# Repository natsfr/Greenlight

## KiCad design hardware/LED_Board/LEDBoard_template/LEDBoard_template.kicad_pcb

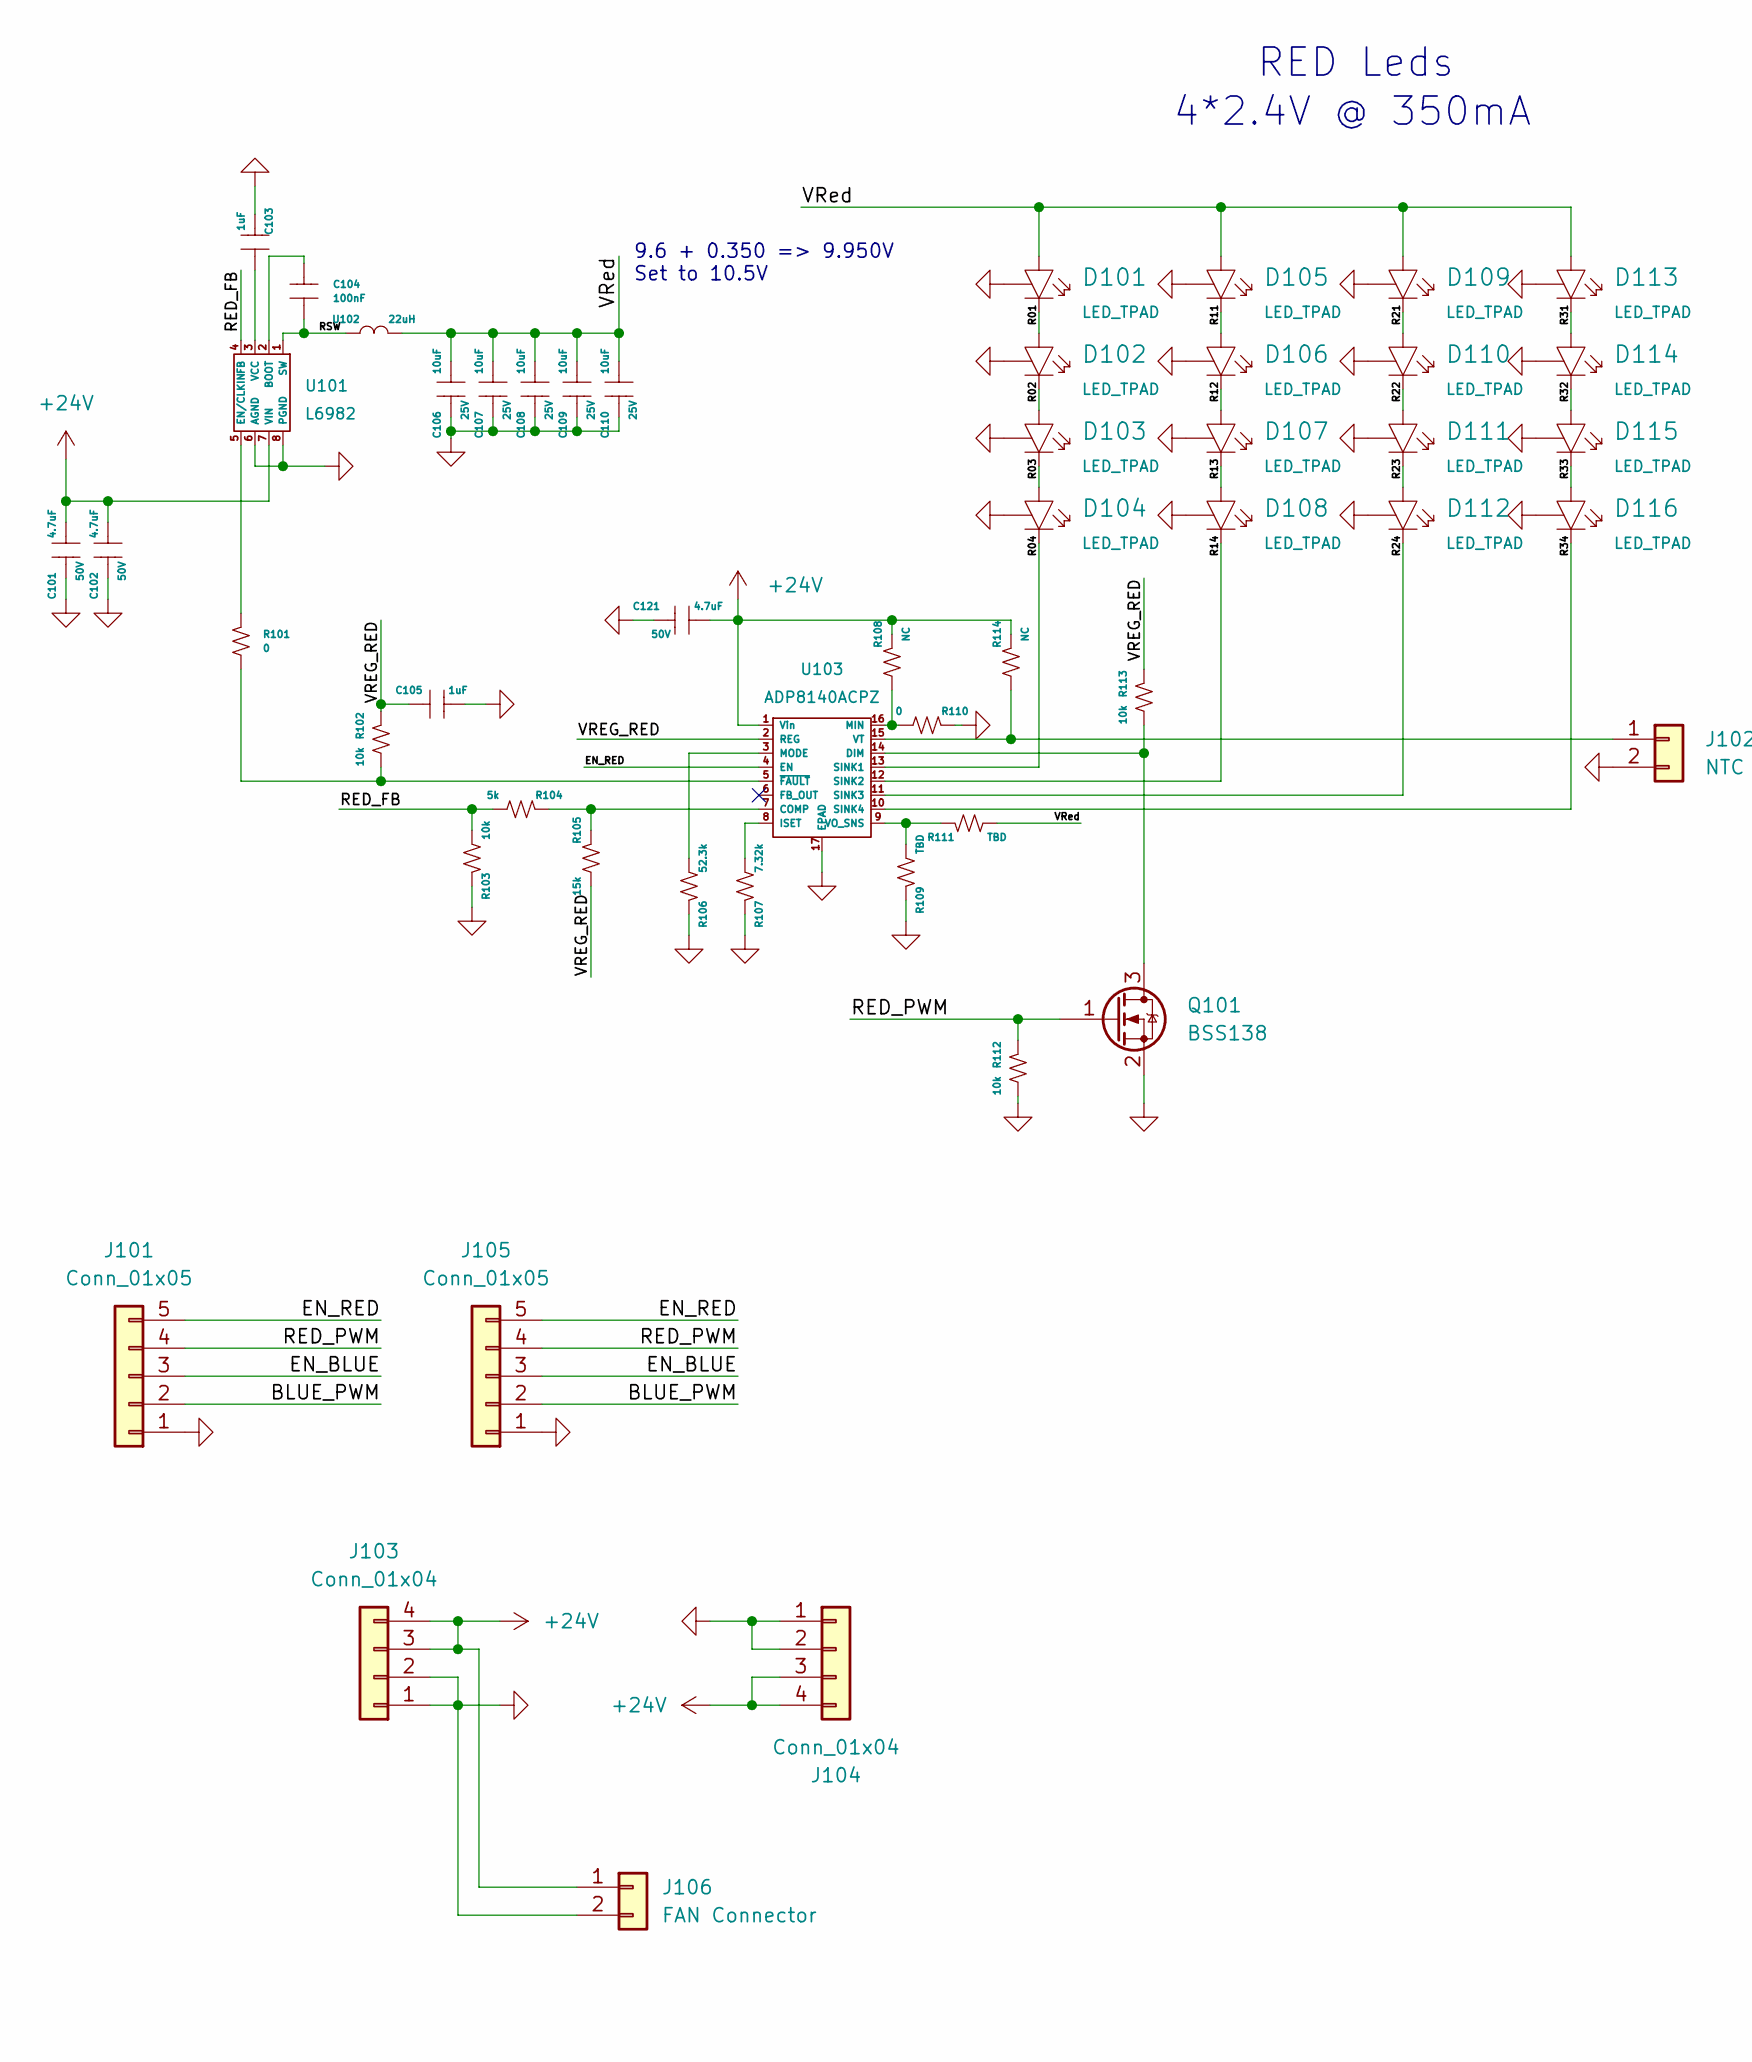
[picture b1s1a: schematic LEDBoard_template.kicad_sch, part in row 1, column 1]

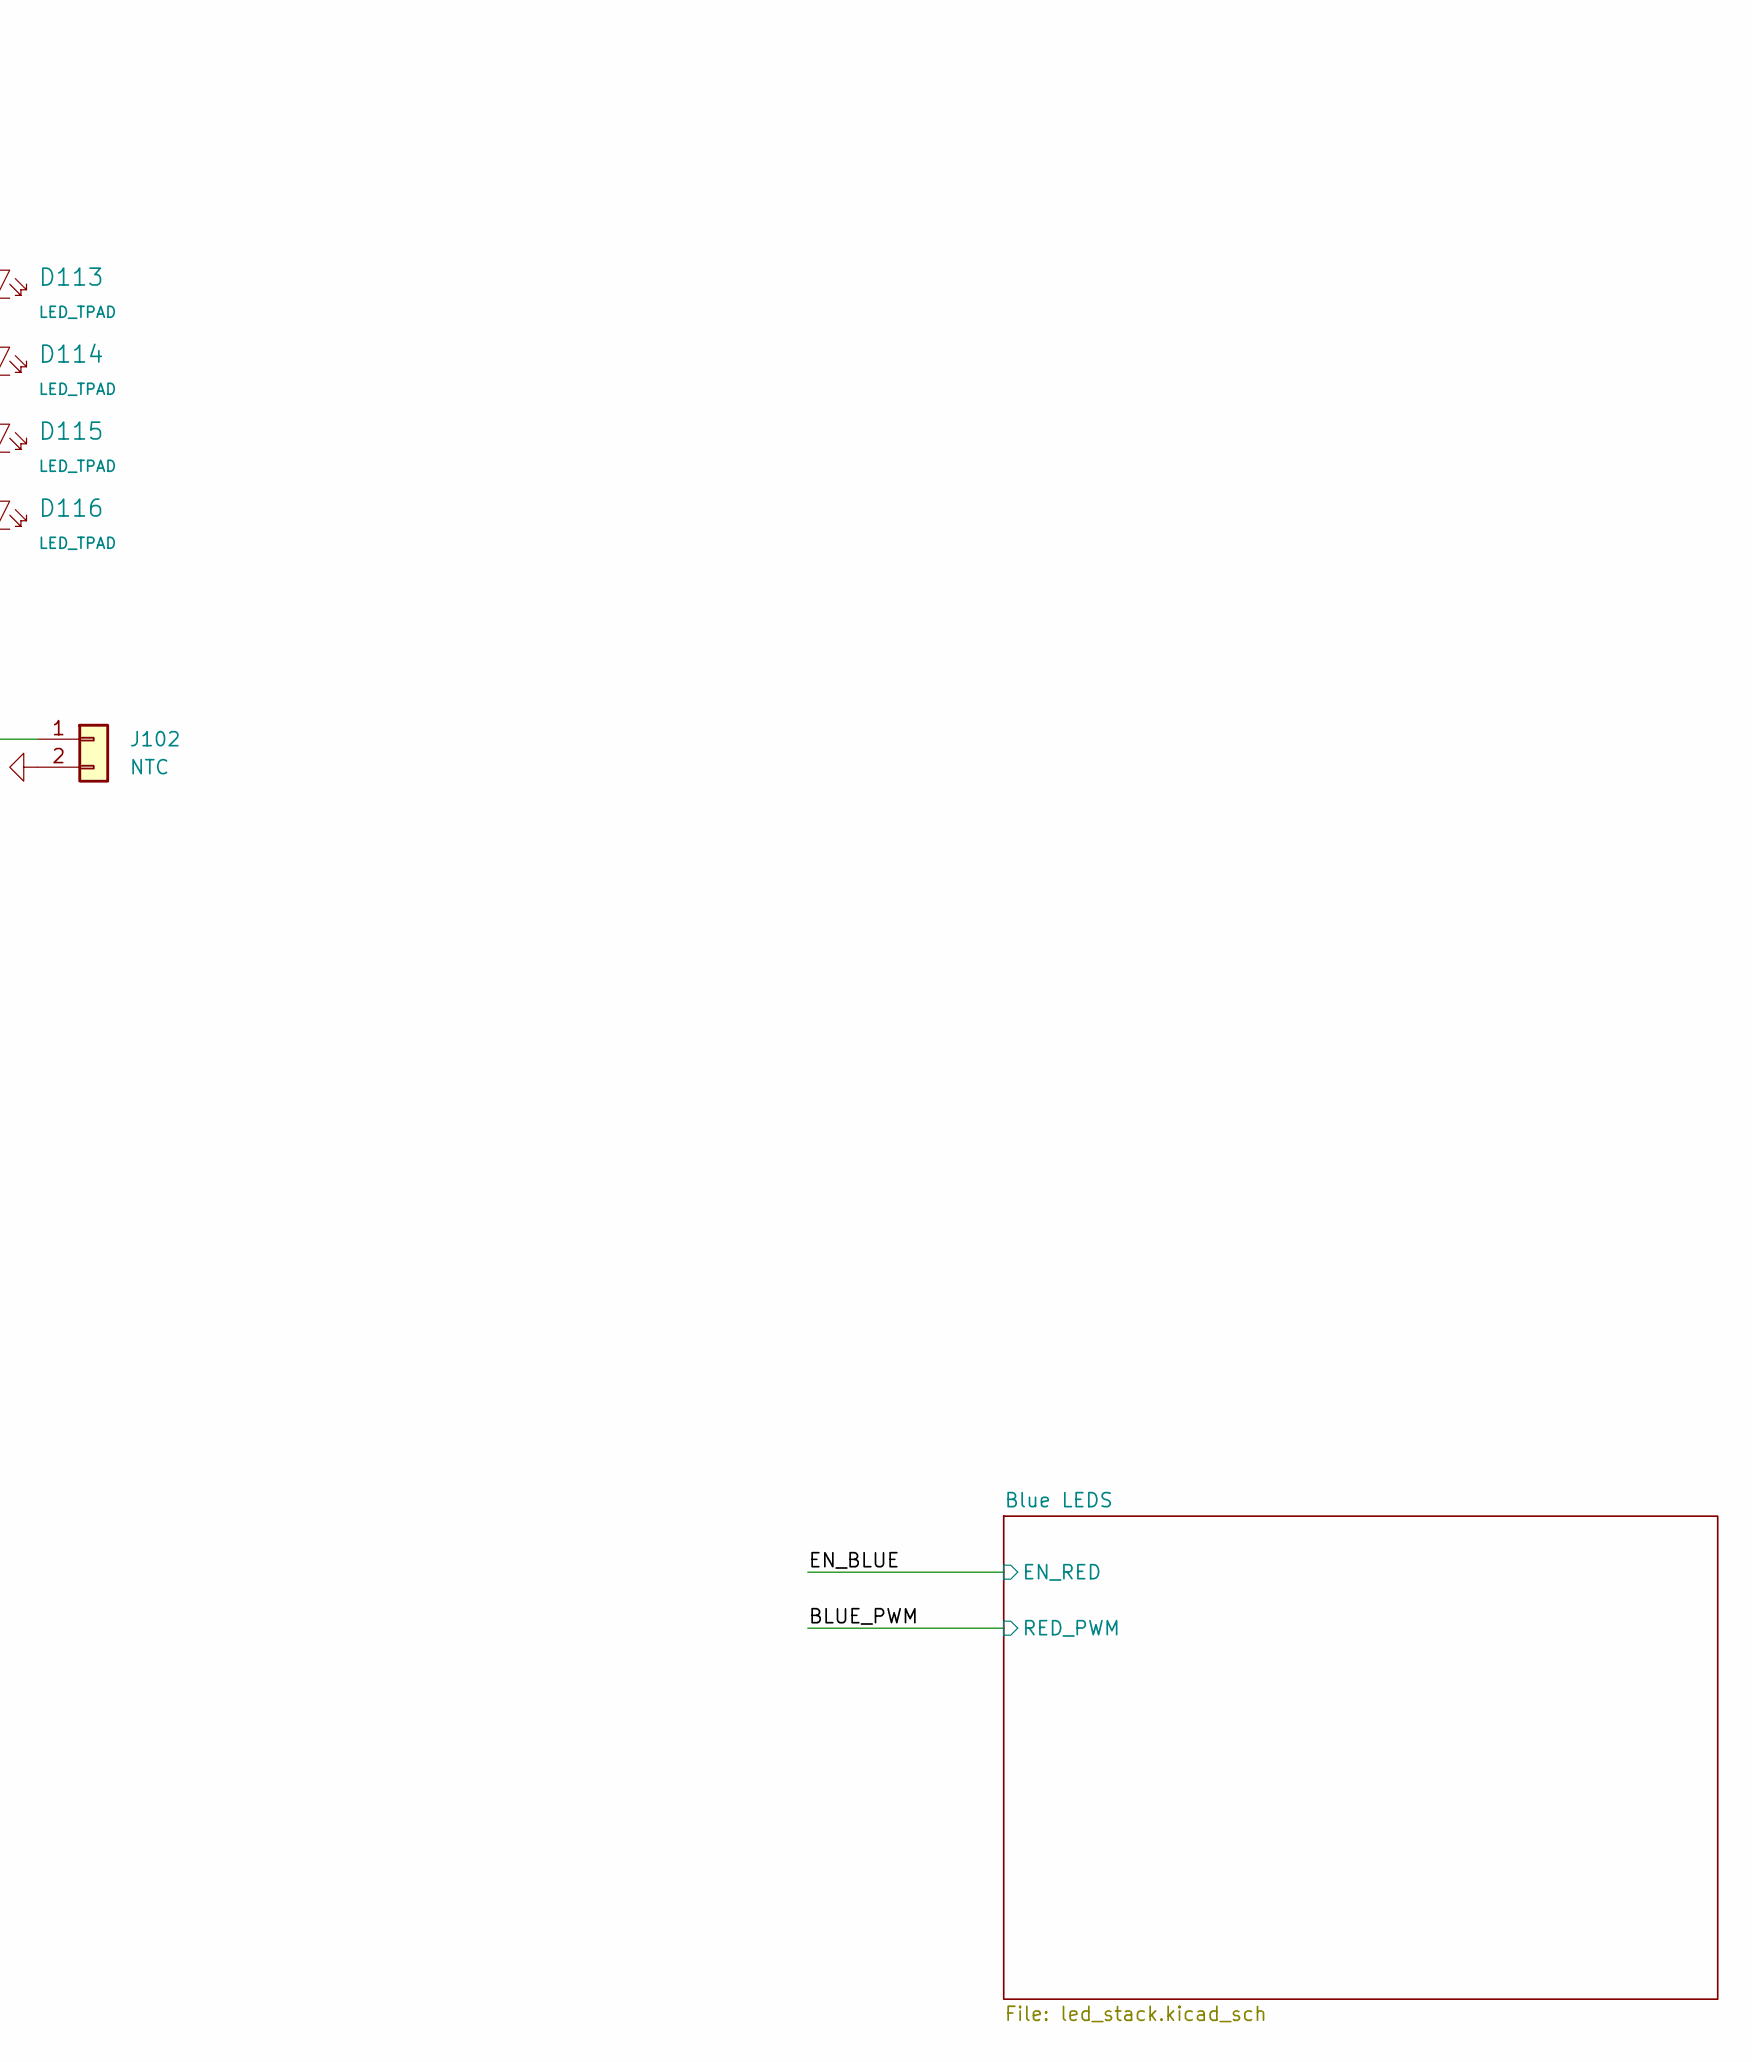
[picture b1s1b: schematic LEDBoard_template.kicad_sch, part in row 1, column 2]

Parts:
C101, C102, C121: 4.7uF; SM1206
C103, C105: 1uF; SM0805
C104: 100nF; SM0603
C106, C107, C108, C109, C110: 10uF; SM1206
D101, D102, D103, D104, D105, D106, D107, D108, D109, D110, D111, D112, D113, D114, D115, D116: LED_TPAD; XLamp_MLE
J101, J105: Conn_01x05; JST_XH_B5B-XH-A_1x05_P2.50mm_Vertical
J102: NTC; JST_XH_B2B-XH-A_1x02_P2.50mm_Vertical
J103, J104: Conn_01x04; MICROFIT_4POS_FEM_43650-0403
J106: FAN Connector; JST_XH_B2B-XH-A_1x02_P2.50mm_Vertical
Q101: BSS138; SOT-23
R101, R110: 0; SM0603
R102, R103, R112, R113: 10k; SM0603
R104: 5k; SM0603
R105: 15k; SM0603
R106: 52.3k; SM0603
R107: 7.32k; SM0603
R108, R114: NC; SM0603
R109, R111: TBD; SM0603
U101: L6982; SOIC-8_208mil
U102: 22uH; IND_SRP8540A_8.1x8.4x3.8mm
U103: ADP8140ACPZ; ADP8140_LFCSP16_4x4_0.4mm

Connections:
+24V: C101.1, C102.1, C121.1, J103.3, J103.4, J104.3, J104.4, J106.1, R108.2, R114.2, U101.7 (VIN), U103.1 (Vin); also elsewhere on the board
/BLUE_PWM: J101.2, J105.2; also elsewhere on the board
/EN_BLUE: J101.3, J105.3; also elsewhere on the board
/EN_RED: J101.5, J105.5, U103.4 (EN)
/R01: D101.K, D102.A
/R02: D102.K, D103.A
/R03: D103.K, D104.A
/R04: D104.K, U103.13 (SINK1)
/R11: D105.K, D106.A
/R12: D106.K, D107.A
/R13: D107.K, D108.A
/R14: D108.K, U103.12 (SINK2)
/R21: D109.K, D110.A
/R22: D110.K, D111.A
/R23: D111.K, D112.A
/R24: D112.K, U103.11 (SINK3)
/R31: D113.K, D114.A
/R32: D114.K, D115.A
/R33: D115.K, D116.A
/R34: D116.K, U103.10 (SINK4)
/RED_FB: R103.1, R104.1, U101.4 (FB)
/RED_PWM: J101.4, J105.4, Q101.1 (G), R112.2
/RSW: C104.1, U101.1 (SW), U102.1
/VREG_RED: C105.1, R102.2, R105.1, R113.2, U103.2 (REG)
/VRed: C106.1, C107.1, C108.1, C109.1, C110.1, D101.A, D105.A, D109.A, D113.A, R111.1, U102.2
GND: C101.2, C102.2, C103.2, C105.2, C106.2, C107.2, C108.2, C109.2, C110.2, C121.2, D101.N (PAD), D102.N (PAD), D103.N (PAD), D104.N (PAD), D105.N (PAD), D106.N (PAD), D107.N (PAD), D108.N (PAD), D109.N (PAD), D110.N (PAD), D111.N (PAD), D112.N (PAD), D113.N (PAD), D114.N (PAD), D115.N (PAD), D116.N (PAD), J101.1, J102.2, J103.1, J103.2, J104.1, J104.2, J105.1, J106.2, Q101.2 (S), R103.2, R106.2, R107.2, R109.2, R110.2, R112.1, U101.6 (AGND), U101.8 (PGND), U103.17 (EPAD); also elsewhere on the board
unnamed: C103.1, U101.3 (VCC)
unnamed: C104.2, U101.2 (BOOT)
unnamed: J102.1, R114.1, U103.15 (VT)
unnamed: Q101.3 (D), R113.1, U103.14 (DIM)
unnamed: R101.1, R102.1, U103.5 (~FAULT)
unnamed: R101.2, U101.5 (EN/CLKIN)
unnamed: R104.2, R105.2, U103.7 (COMP)
unnamed: R106.1, U103.3 (MODE)
unnamed: R107.1, U103.8 (ISET)
unnamed: R108.1, R110.1, U103.16 (MIN)
unnamed: R109.1, R111.2, U103.9 (VO_SNS)

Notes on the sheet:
9.6 + 0.350 => 9.950V Set to 10.5V
4*2.4V @ 350mA
RED Leds

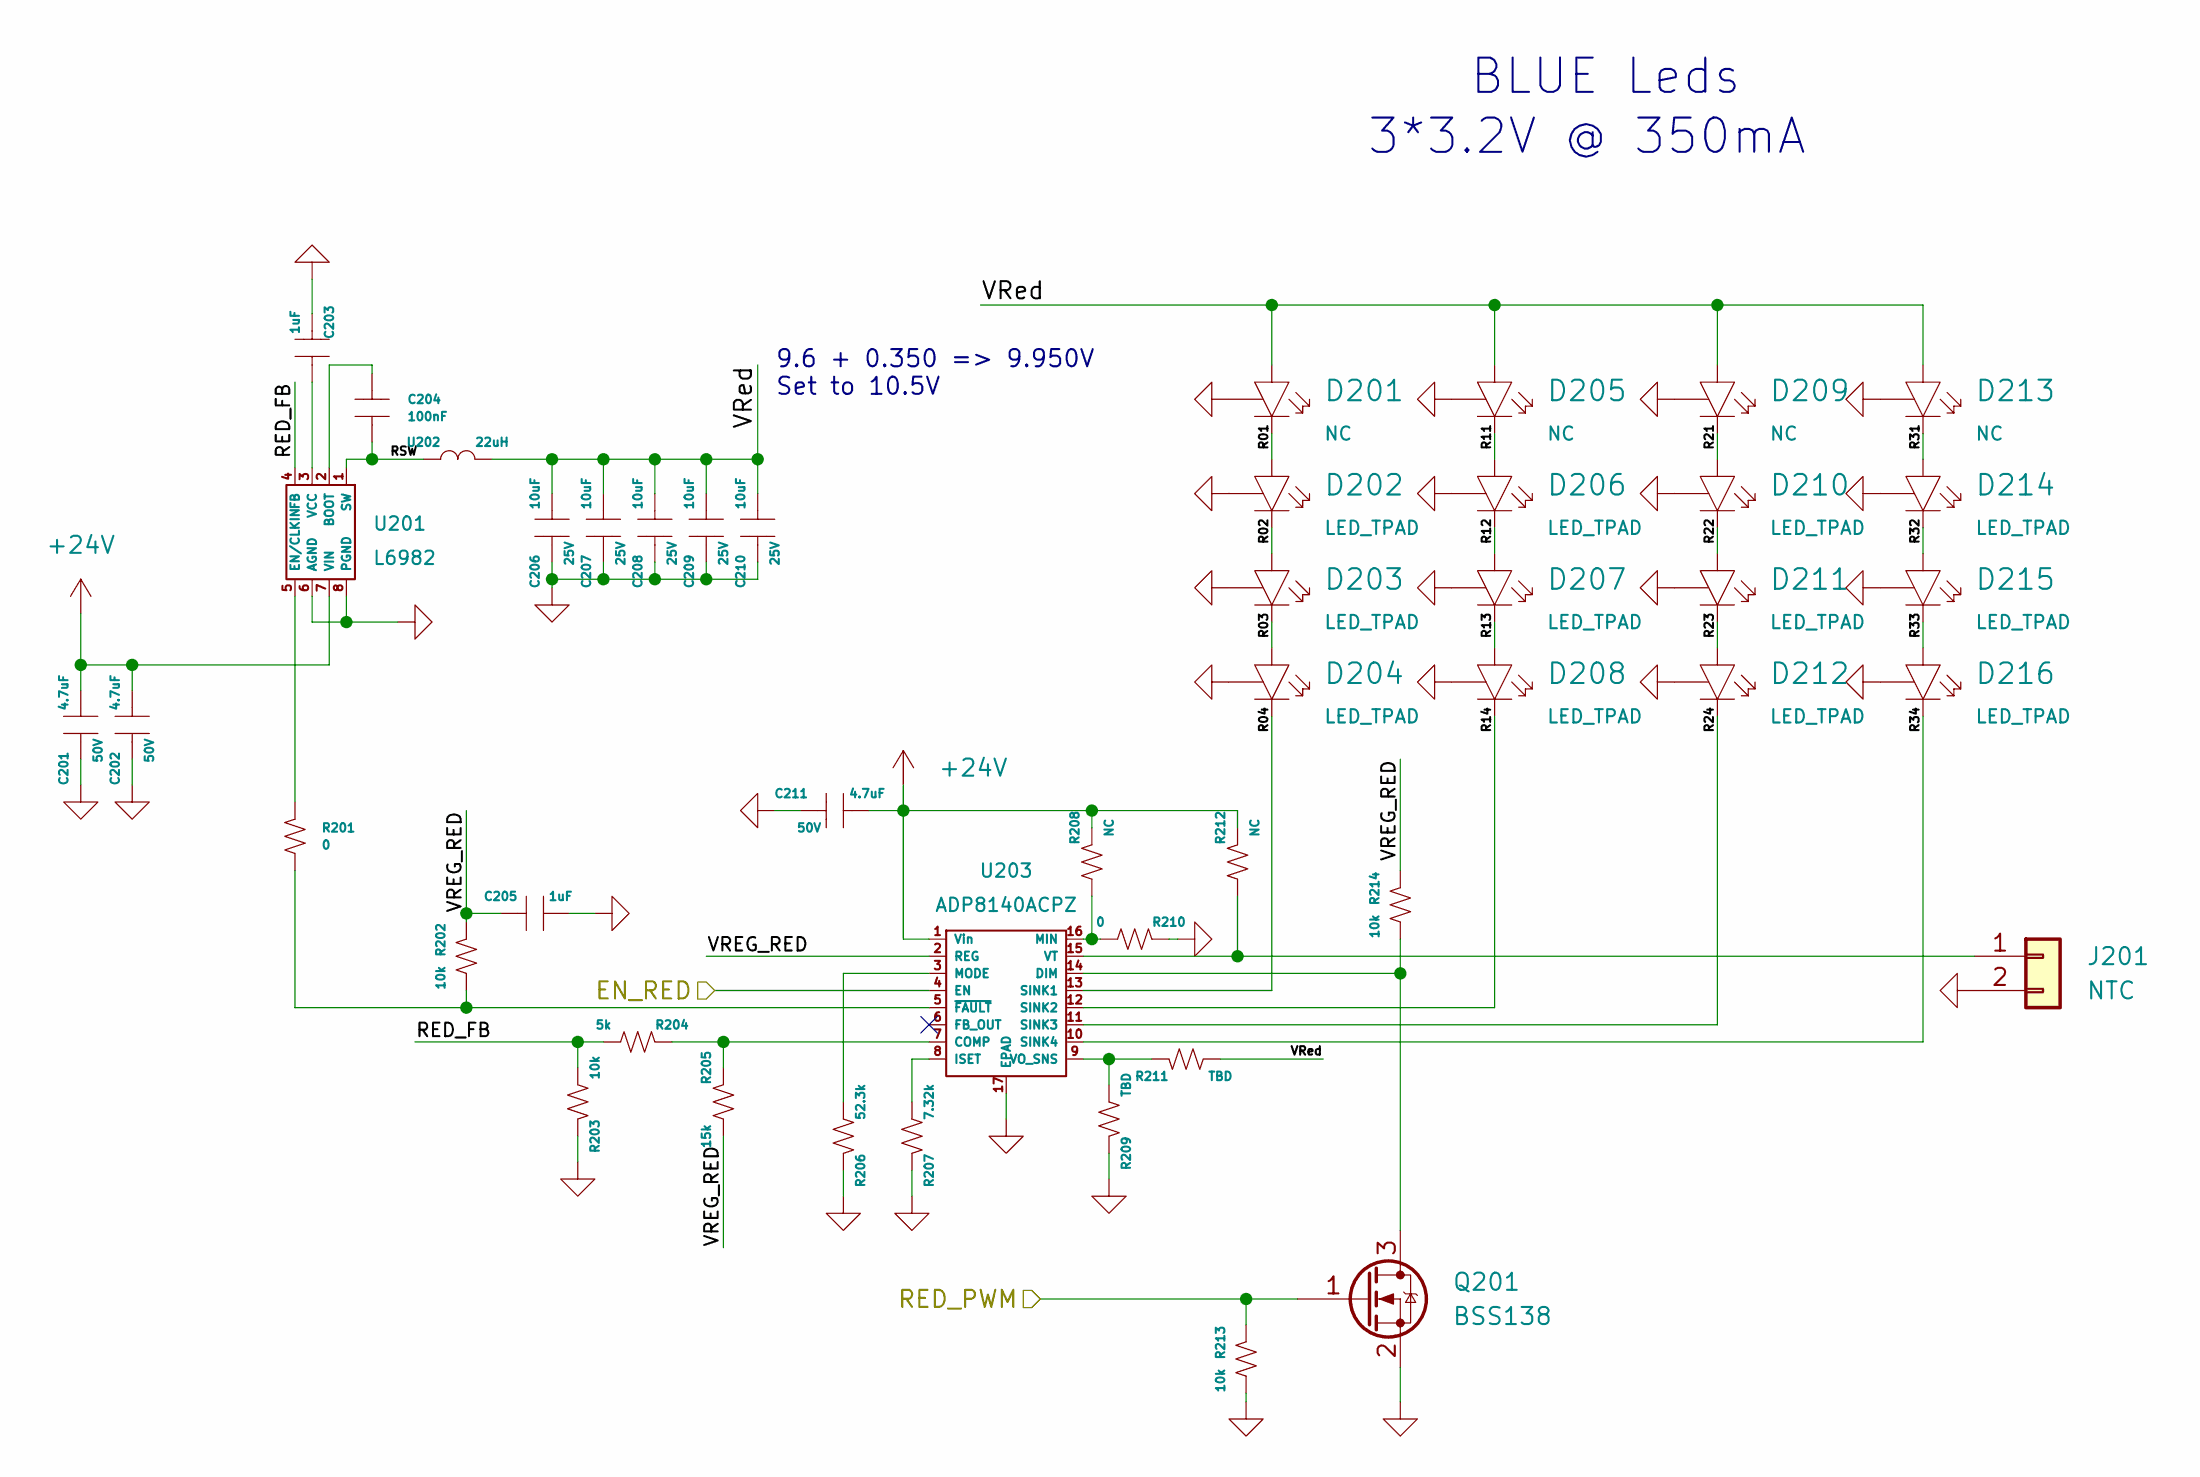
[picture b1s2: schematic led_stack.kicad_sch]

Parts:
C201, C202, C211: 4.7uF; SM1206
C203, C205: 1uF; SM0805
C204: 100nF; SM0603
C206, C207, C208, C209, C210: 10uF; SM1206
D201, D205, D209, D213: NC; XLamp_MLE
D202, D203, D204, D206, D207, D208, D210, D211, D212, D214, D215, D216: LED_TPAD; XLamp_MLE
J201: NTC; JST_XH_B2B-XH-A_1x02_P2.50mm_Vertical
Q201: BSS138; SOT-23
R201, R210: 0; SM0603
R202, R203, R213, R214: 10k; SM0603
R204: 5k; SM0603
R205: 15k; SM0603
R206: 52.3k; SM0603
R207: 7.32k; SM0603
R208, R212: NC; SM0603
R209, R211: TBD; SM0603
U201: L6982; SOIC-8_208mil
U202: 22uH; IND_SRP8540A_8.1x8.4x3.8mm
U203: ADP8140ACPZ; ADP8140_LFCSP16_4x4_0.4mm

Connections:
+24V: C201.1, C202.1, C211.1, R208.2, R212.2, U201.7 (VIN), U203.1 (Vin); also elsewhere on the board
/BLUE_PWM: Q201.1 (G), R213.2; also elsewhere on the board
/Blue LEDS/R01: D201.K, D202.A
/Blue LEDS/R02: D202.K, D203.A
/Blue LEDS/R03: D203.K, D204.A
/Blue LEDS/R04: D204.K, U203.13 (SINK1)
/Blue LEDS/R11: D205.K, D206.A
/Blue LEDS/R12: D206.K, D207.A
/Blue LEDS/R13: D207.K, D208.A
/Blue LEDS/R14: D208.K, U203.12 (SINK2)
/Blue LEDS/R21: D209.K, D210.A
/Blue LEDS/R22: D210.K, D211.A
/Blue LEDS/R23: D211.K, D212.A
/Blue LEDS/R24: D212.K, U203.11 (SINK3)
/Blue LEDS/R31: D213.K, D214.A
/Blue LEDS/R32: D214.K, D215.A
/Blue LEDS/R33: D215.K, D216.A
/Blue LEDS/R34: D216.K, U203.10 (SINK4)
/Blue LEDS/RED_FB: R203.1, R204.1, U201.4 (FB)
/Blue LEDS/RSW: C204.1, U201.1 (SW), U202.1
/Blue LEDS/VREG_RED: C205.1, R202.2, R205.1, R214.2, U203.2 (REG)
/Blue LEDS/VRed: C206.1, C207.1, C208.1, C209.1, C210.1, D201.A, D205.A, D209.A, D213.A, R211.1, U202.2
/EN_BLUE: U203.4 (EN); also elsewhere on the board
GND: C201.2, C202.2, C203.2, C205.2, C206.2, C207.2, C208.2, C209.2, C210.2, C211.2, D201.N (PAD), D202.N (PAD), D203.N (PAD), D204.N (PAD), D205.N (PAD), D206.N (PAD), D207.N (PAD), D208.N (PAD), D209.N (PAD), D210.N (PAD), D211.N (PAD), D212.N (PAD), D213.N (PAD), D214.N (PAD), D215.N (PAD), D216.N (PAD), J201.2, Q201.2 (S), R203.2, R206.2, R207.2, R209.2, R210.2, R213.1, U201.6 (AGND), U201.8 (PGND), U203.17 (EPAD); also elsewhere on the board
unnamed: C203.1, U201.3 (VCC)
unnamed: C204.2, U201.2 (BOOT)
unnamed: J201.1, R212.1, U203.15 (VT)
unnamed: Q201.3 (D), R214.1, U203.14 (DIM)
unnamed: R201.1, R202.1, U203.5 (~FAULT)
unnamed: R201.2, U201.5 (EN/CLKIN)
unnamed: R204.2, R205.2, U203.7 (COMP)
unnamed: R206.1, U203.3 (MODE)
unnamed: R207.1, U203.8 (ISET)
unnamed: R208.1, R210.1, U203.16 (MIN)
unnamed: R209.1, R211.2, U203.9 (VO_SNS)

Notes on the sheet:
BLUE Leds
3*3.2V @ 350mA
9.6 + 0.350 => 9.950V Set to 10.5V

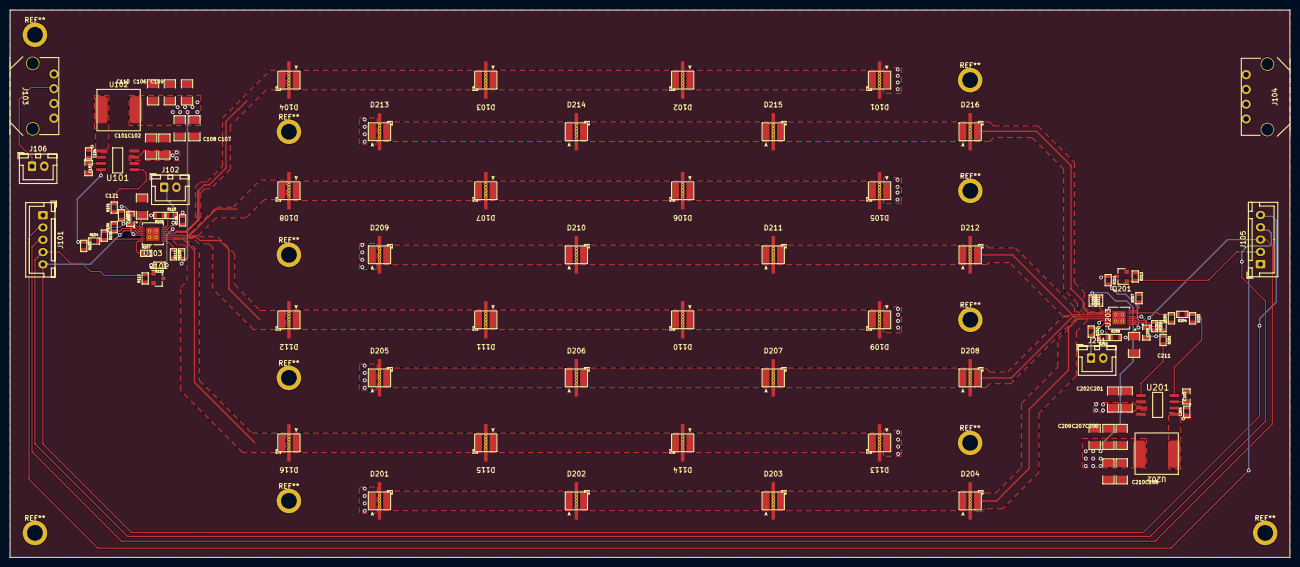
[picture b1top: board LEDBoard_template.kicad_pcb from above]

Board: 4 copper layers, 260.0 x 111.2 mm, 97 parts (0 on the bottom side), 68 nets.

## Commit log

2022-07-10 first commit of greenlight project
2022-10-09 Working lamp pcb
